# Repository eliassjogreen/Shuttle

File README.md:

# Shuttle
🚀 Shuttle 3x4 12 key numpad

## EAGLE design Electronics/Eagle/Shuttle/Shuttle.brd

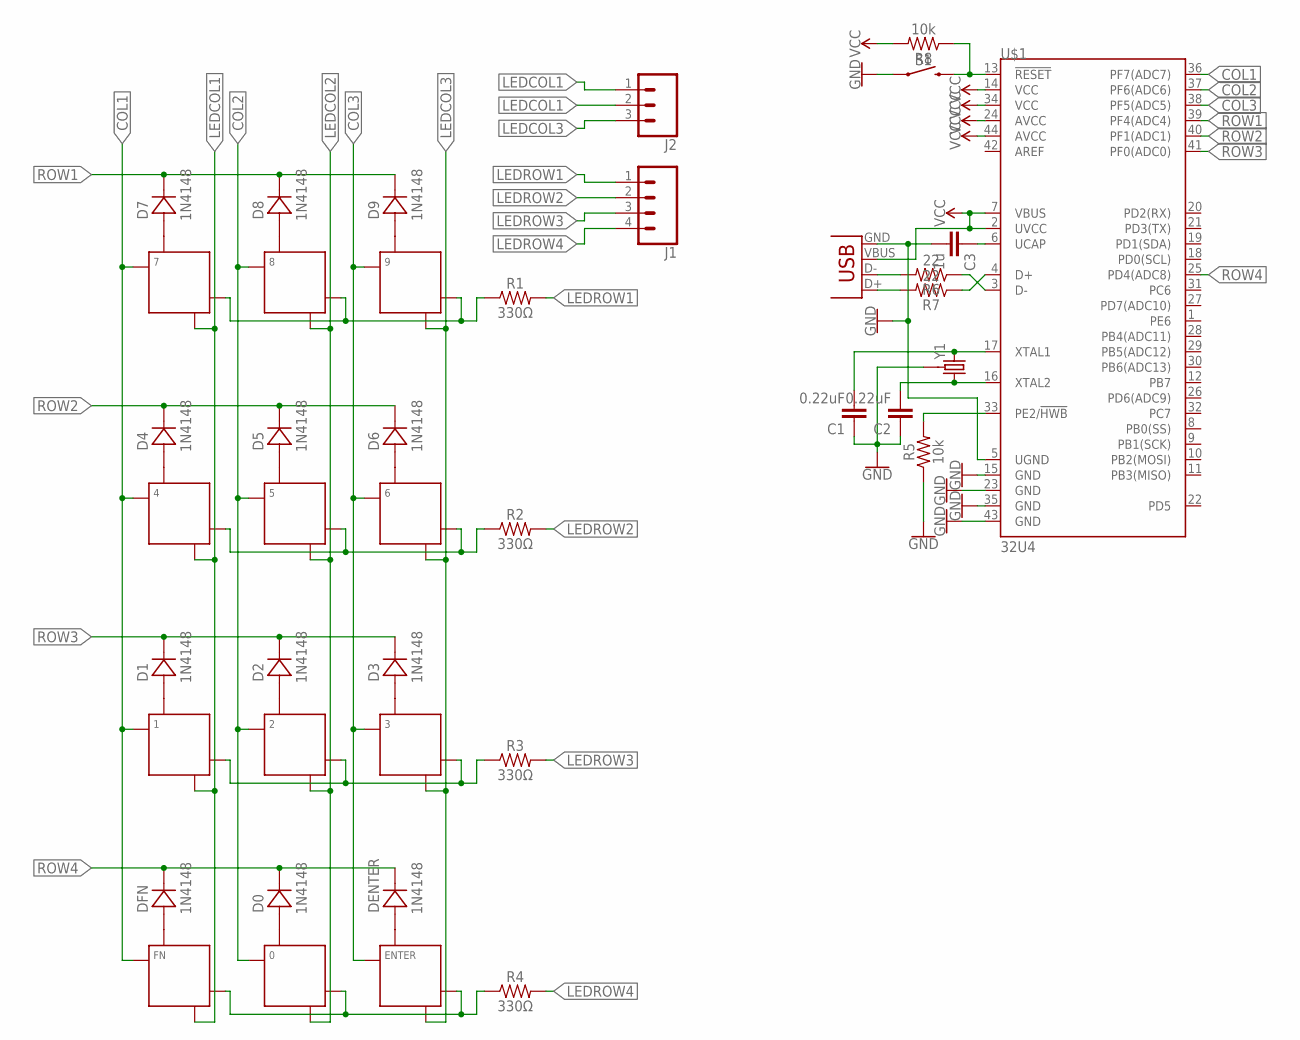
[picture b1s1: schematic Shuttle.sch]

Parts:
0, 1, 2, 3, 4, 5, 6, 7, 8, 9: KEYSWITCH-LED-ALPSMX-1U-LED; ALPSMX-1U-LED
C1, C2: 0.22uF; 0603
C3: 1u; 0603
D0, D1, D2, D3, D4, D5, D6, D7, D8, D9: 1N4148; DO-35
DENTER: 1N4148; DO-35
DFN: 1N4148; DO-35
ENTER: KEYSWITCH-LED-ALPSMX-1U-LED; ALPSMX-1U-LED
FN: KEYSWITCH-LED-ALPSMX-1U-LED; ALPSMX-1U-LED
J1: CONN_04; 1X04
J2: CONN_03; 1X03
R1, R2, R3, R4: 330Ω; AXIAL-0.3
R5, R8: 10k; AXIAL-0.3
R6, R7: 22; AXIAL-0.3
S1: MOMENTARY-SWITCH-SPST-PTH-6.0MM; TACTILE_SWITCH_PTH_6.0MM
U$1: 32U4; TQFP44
X1: USB-MB-H
Y1: CRYSTAL-GROUNDEDSMD-5X3.2; CRYSTAL-SMD-5X3.2-4PAD

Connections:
COL1: 1.ALPS1 (P0), 1.MX1 (P0), 4.ALPS1 (P0), 4.MX1 (P0), 7.ALPS1 (P0), 7.MX1 (P0), FN.ALPS1 (P0), FN.MX1 (P0), U$1.36 (PF7(ADC7))
COL2: 0.ALPS1 (P0), 0.MX1 (P0), 2.ALPS1 (P0), 2.MX1 (P0), 5.ALPS1 (P0), 5.MX1 (P0), 8.ALPS1 (P0), 8.MX1 (P0), U$1.37 (PF6(ADC6))
COL3: 3.ALPS1 (P0), 3.MX1 (P0), 6.ALPS1 (P0), 6.MX1 (P0), 9.ALPS1 (P0), 9.MX1 (P0), ENTER.ALPS1 (P0), ENTER.MX1 (P0), U$1.38 (PF5(ADC5))
GND: C1.1, C2.1, C3.2, R5.P$1 (1), S1.1, U$1.5 (UGND), U$1.15 (GND), U$1.23 (GND), U$1.35 (GND), U$1.43 (GND), X1.GND, Y1.2 (3), Y1.4 (3)
LEDCOL1: 1.LED+, 4.LED+, 7.LED+, FN.LED+, J2.1, J2.2
LEDCOL2: 0.LED+, 2.LED+, 5.LED+, 8.LED+
LEDCOL3: 3.LED+, 6.LED+, 9.LED+, ENTER.LED+, J2.3
LEDROW1: J1.1, R1.P$2 (2)
LEDROW2: J1.2, R2.P$2 (2)
LEDROW3: J1.3, R3.P$2 (2)
LEDROW4: J1.4, R4.P$2 (2)
unnamed: 7.ALPS2 (P1), 7.MX2 (P1), D7.A
unnamed: 8.ALPS2 (P1), 8.MX2 (P1), D8.A
unnamed: 9.ALPS2 (P1), 9.MX2 (P1), D9.A
unnamed: 4.ALPS2 (P1), 4.MX2 (P1), D4.A
unnamed: 5.ALPS2 (P1), 5.MX2 (P1), D5.A
unnamed: 6.ALPS2 (P1), 6.MX2 (P1), D6.A
unnamed: 1.ALPS2 (P1), 1.MX2 (P1), D1.A
unnamed: 2.ALPS2 (P1), 2.MX2 (P1), D2.A
unnamed: 3.ALPS2 (P1), 3.MX2 (P1), D3.A
unnamed: DFN.A, FN.ALPS2 (P1), FN.MX2 (P1)
unnamed: 0.ALPS2 (P1), 0.MX2 (P1), D0.A
unnamed: DENTER.A, ENTER.ALPS2 (P1), ENTER.MX2 (P1)
unnamed: C2.2, U$1.16 (XTAL2), Y1.1 (2)
unnamed: 7.LED-, 8.LED-, 9.LED-, R1.P$1 (1)
unnamed: R7.P$2 (2), X1.D+
unnamed: R7.P$1 (1), U$1.4 (D+)
unnamed: C1.2, U$1.17 (XTAL1), Y1.3 (1)
unnamed: 4.LED-, 5.LED-, 6.LED-, R2.P$1 (1)
unnamed: R5.P$2 (2), U$1.33 (PE2/!HWB)
unnamed: R6.P$2 (2), X1.D-
unnamed: R6.P$1 (1), U$1.3 (D-)
unnamed: C3.1, U$1.6 (UCAP)
unnamed: R8.P$1 (1), S1.3 (2), U$1.13 (!RESET)
unnamed: 1.LED-, 2.LED-, 3.LED-, R3.P$1 (1)
unnamed: 0.LED-, ENTER.LED-, FN.LED-, R4.P$1 (1)
ROW1: D7.C, D8.C, D9.C, U$1.39 (PF4(ADC4))
ROW2: D4.C, D5.C, D6.C, U$1.40 (PF1(ADC1))
ROW3: D1.C, D2.C, D3.C, U$1.41 (PF0(ADC0))
ROW4: D0.C, DENTER.C, DFN.C, U$1.25 (PD4(ADC8))
VCC: R8.P$2 (2), U$1.2 (UVCC), U$1.7 (VBUS), U$1.14 (VCC), U$1.24 (AVCC), U$1.34 (VCC), U$1.44 (AVCC), X1.VBUS

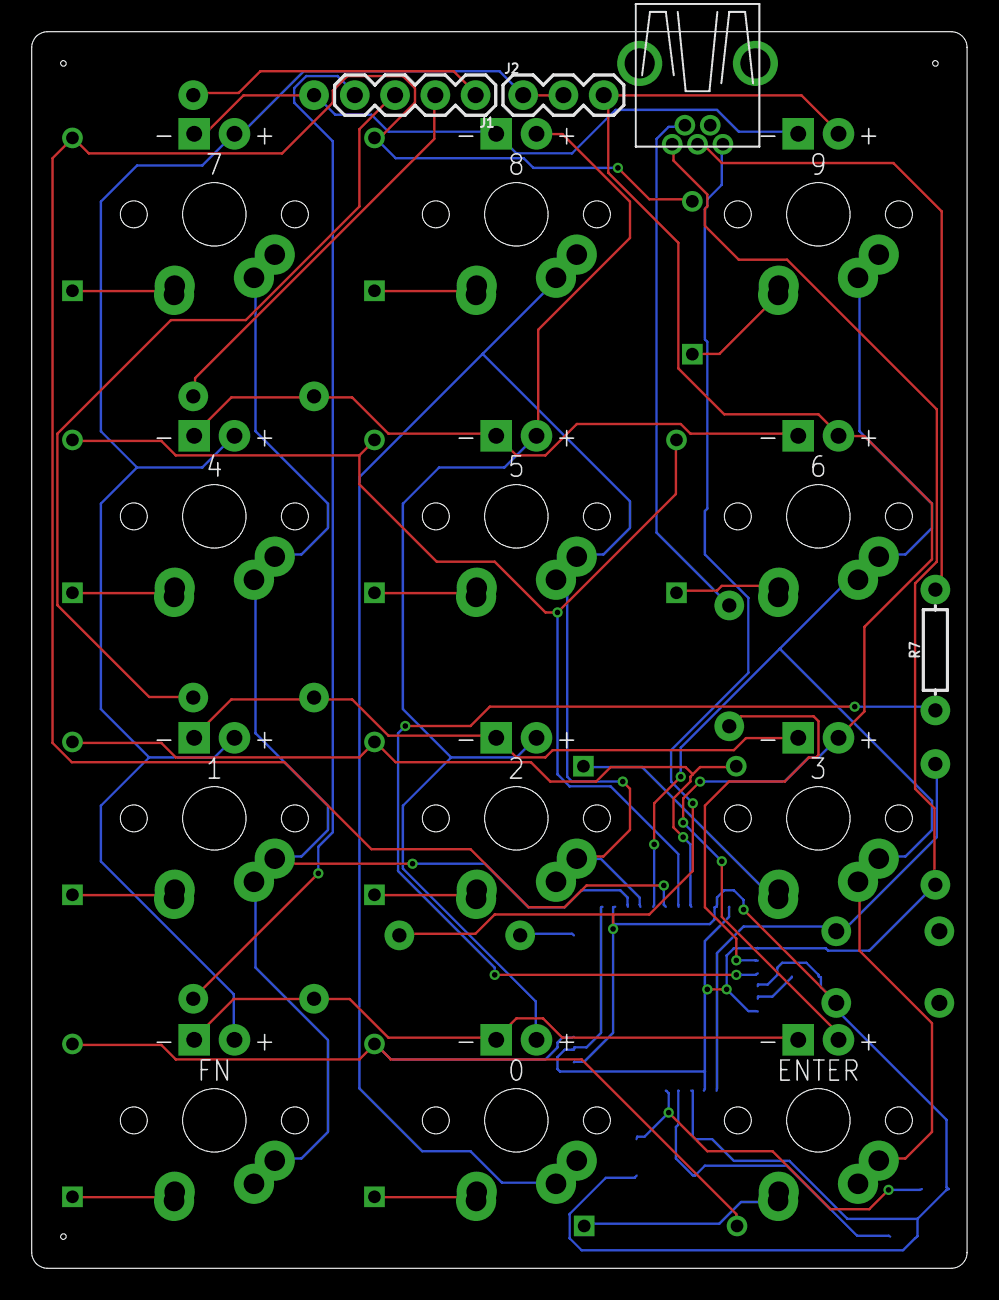
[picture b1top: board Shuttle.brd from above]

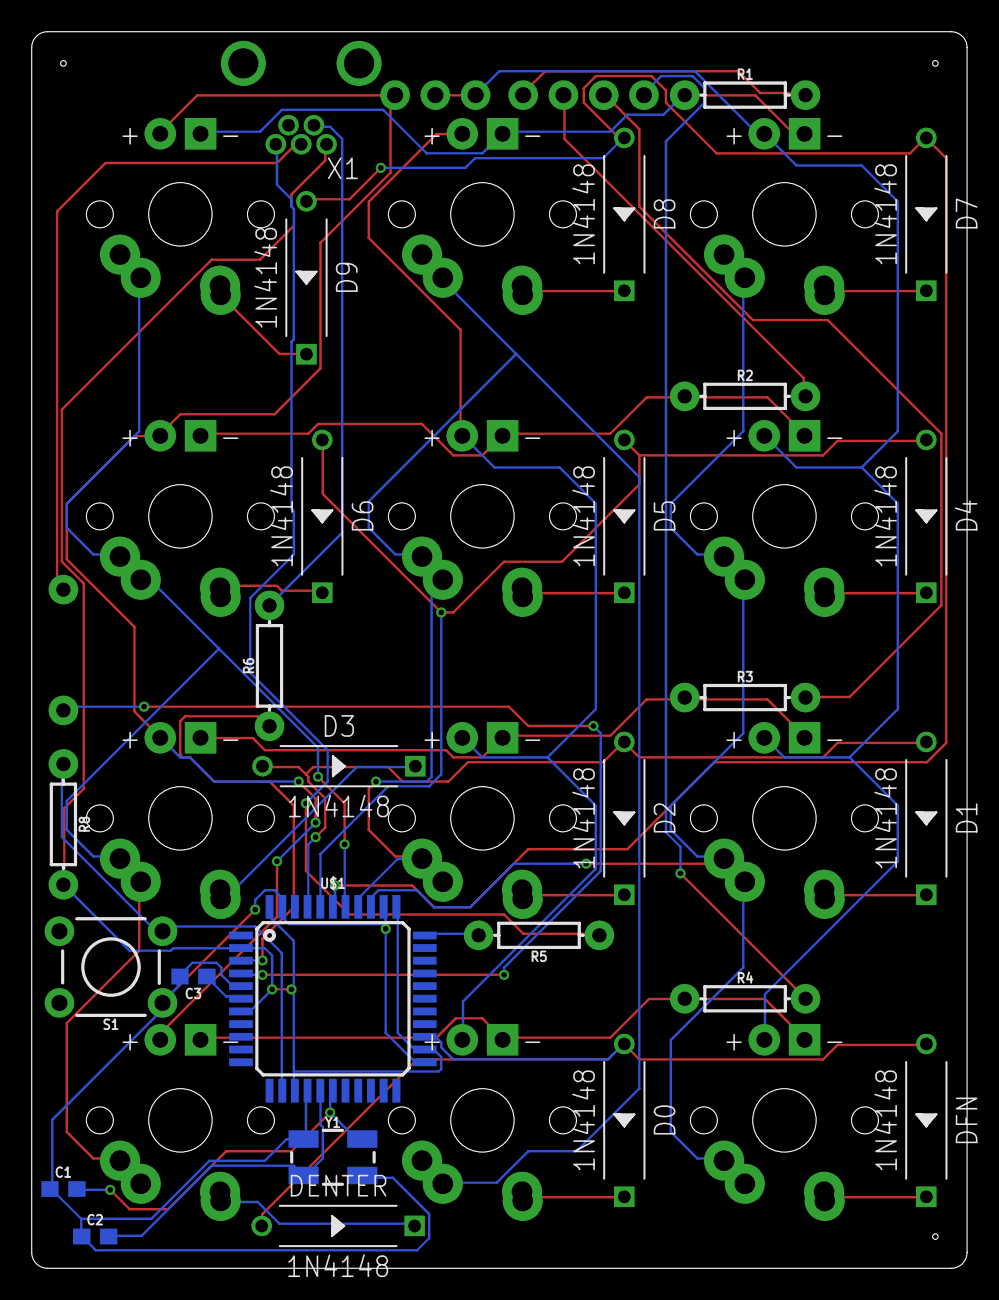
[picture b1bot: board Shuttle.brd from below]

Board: 2 copper layers, 59.0 x 78.0 mm, 41 parts (26 on the bottom side), 41 nets.

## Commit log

2017-10-10 Added images
2017-10-24 Added top plates for prototyping
2017-10-31 Added images and blender models
2017-11-03 Create LICENSE

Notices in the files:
parts and their libraries:
SparkFun-Resistors: Licensing: Creative Commons ShareAlike 4.0 International - https://creativecommons.org/licenses/by-sa/4.0
